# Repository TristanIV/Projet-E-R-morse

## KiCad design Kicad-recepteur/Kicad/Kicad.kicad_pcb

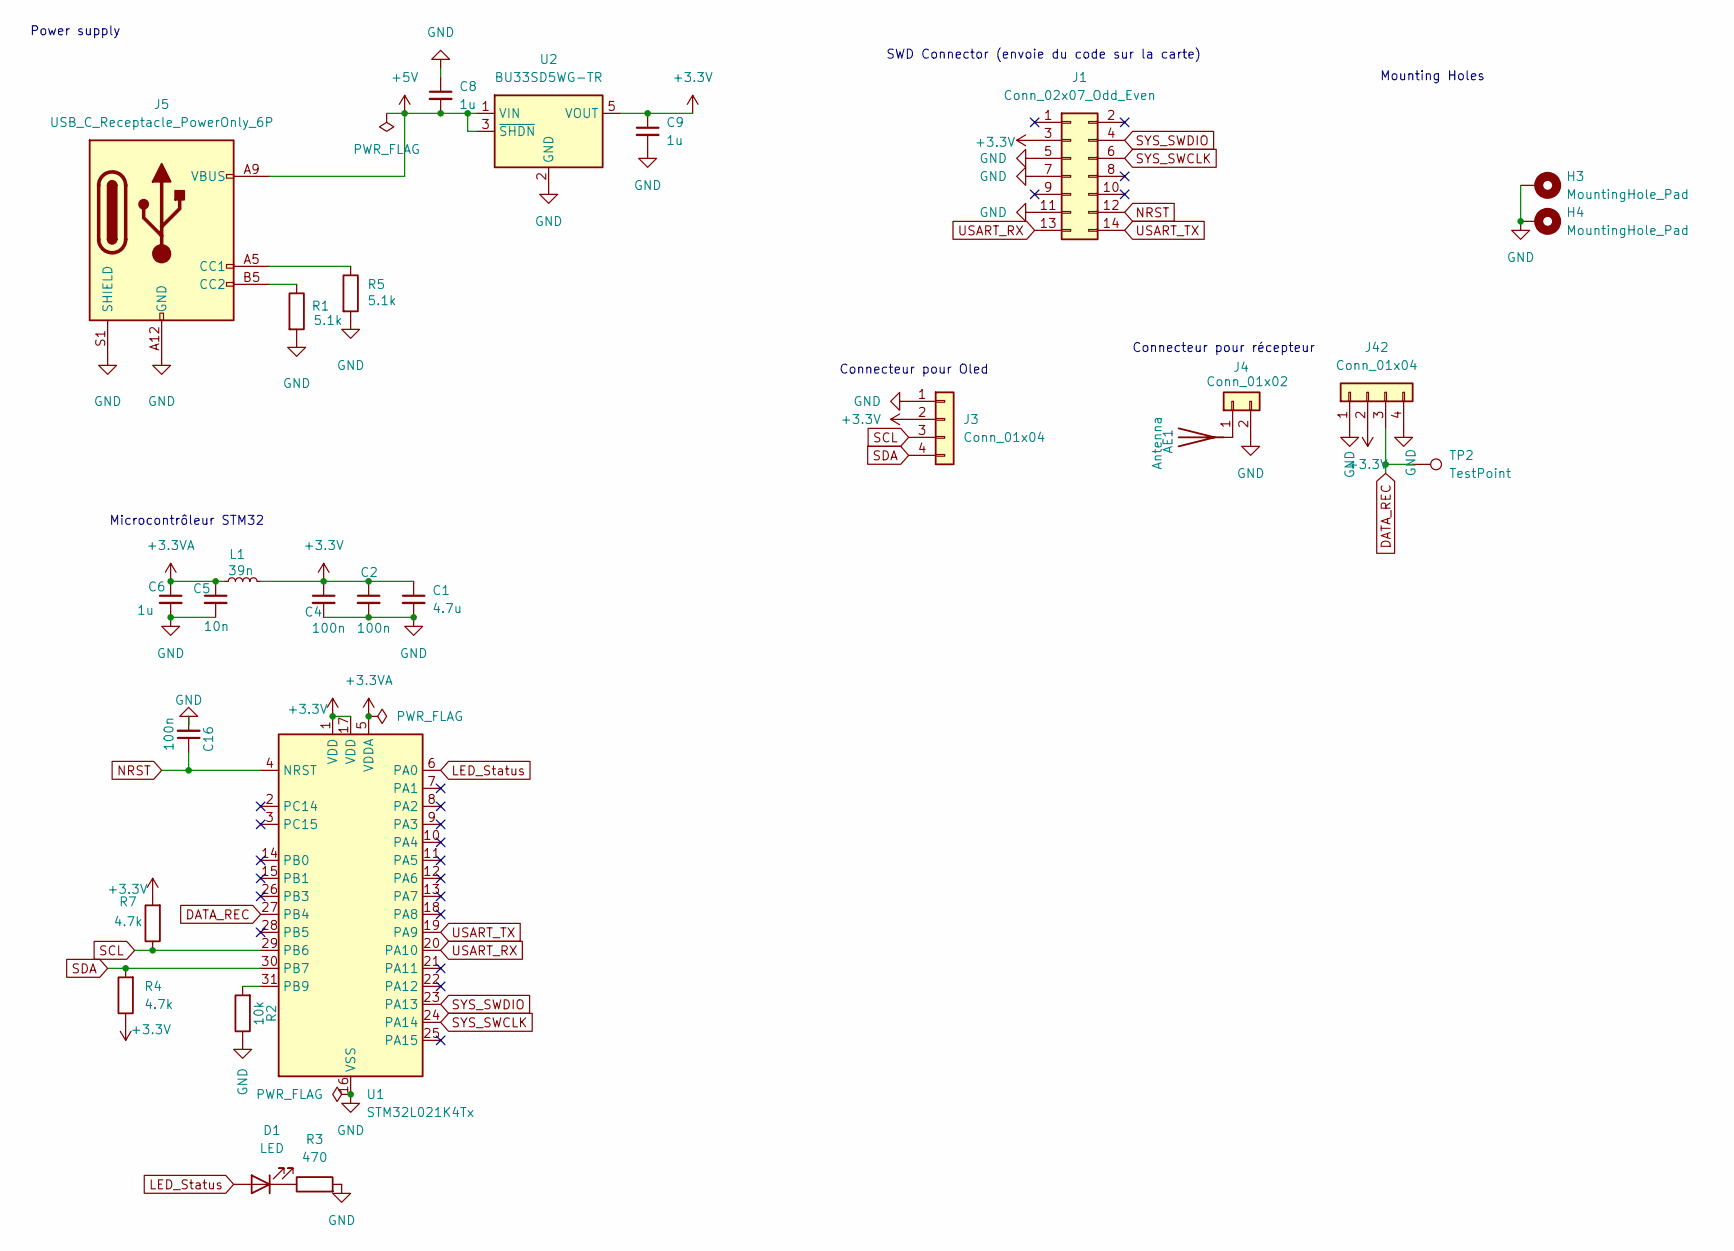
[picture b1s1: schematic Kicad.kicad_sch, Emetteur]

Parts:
AE1: Antenna; SolderWire-0.5sqmm_1x01_D0.9mm_OD2.3mm
C1: 4.7u; C_0603_1608Metric_Pad1.08x0.95mm_HandSolder
C2, C4, C16: 100n; C_0603_1608Metric_Pad1.08x0.95mm_HandSolder
C5: 10n; C_0603_1608Metric_Pad1.08x0.95mm_HandSolder
C6, C8, C9: 1u; C_0603_1608Metric_Pad1.08x0.95mm_HandSolder
D1: LED; LED_0603_1608Metric
H3, H4: MountingHole_Pad; MountingHole_3.2mm_M3_DIN965_Pad
J1: Conn_02x07_Odd_Even; PinHeader_2x07_P1.27mm_Vertical_SMD
J3, J42: Conn_01x04; PinSocket_1x04_P2.54mm_Vertical
J4: Conn_01x02; SolderWire-0.5sqmm_1x02_P4.6mm_D0.9mm_OD2.1mm
J5: USB_C_Receptacle_PowerOnly_6P; USB_C_Receptacle_GCT_USB4125-xx-x-0190_6P_TopMnt_Horizontal
L1: 39n; L_0805_2012Metric_Pad1.05x1.20mm_HandSolder
R1, R5: 5.1k; R_0603_1608Metric_Pad0.98x0.95mm_HandSolder
R2: 10k; R_0603_1608Metric_Pad0.98x0.95mm_HandSolder
R3: 470; R_0603_1608Metric_Pad0.98x0.95mm_HandSolder
R4, R7: 4.7k; R_0603_1608Metric_Pad0.98x0.95mm_HandSolder
TP2: TestPoint; TestPoint_Loop_D2.50mm_Drill1.0mm
U1: STM32L021K4Tx; LQFP-32_7x7mm_P0.8mm
U2: BU33SD5WG-TR; SOT-23-5

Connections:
+3.3V: C1.1, C2.1, C4.1, C9.1, J1.3, J3.2, J42.2, L1.2, R4.1, R7.2, U1.1 (VDD), U1.17 (VDD), U2.5 (VOUT)
+3.3VA: C5.1, C6.1, L1.1, U1.5 (VDDA)
+5V: C8.2, J5.A9 (VBUS), J5.B9 (VBUS), U2.1 (VIN), U2.3 (~SHDN)
DATA_REC: J42.3, TP2.1, U1.27 (PB4)
GND: C1.2, C2.2, C4.2, C5.2, C6.2, C8.1, C9.2, C16.2, H3.1, H4.1, J1.5, J1.7, J1.11, J3.1, J4.2, J5.A12 (GND), J5.B12 (GND), J5.S1 (SHIELD), J42.1, J42.4, R1.2, R2.1, R3.2, R5.2, U1.16 (VSS), U1.32 (VSS), U2.2 (GND)
LED_Status: D1.2 (A), U1.6 (PA0)
NRST: C16.1, J1.12, U1.4 (NRST)
unnamed: AE1.1 (A), J4.1
unnamed: D1.1 (K), R3.1
unnamed: J5.A5 (CC1), R5.1
unnamed: J5.B5 (CC2), R1.1
unnamed: R2.2, U1.31 (PB9)
SCL: J3.3, R7.1, U1.29 (PB6)
SDA: J3.4, R4.2, U1.30 (PB7)
SYS_SWCLK: J1.6, U1.24 (PA14)
SYS_SWDIO: J1.4, U1.23 (PA13)
USART_RX: J1.13, U1.20 (PA10)
USART_TX: J1.14, U1.19 (PA9)

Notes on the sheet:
Connecteur pour Oled
Power supply
SWD Connector (envoie du code sur la carte)
Microcontrôleur STM32
Connecteur pour récepteur
Mounting Holes

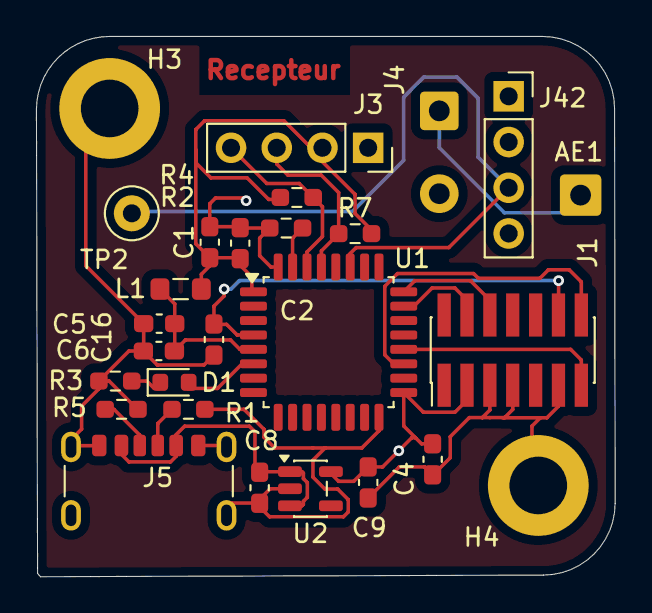
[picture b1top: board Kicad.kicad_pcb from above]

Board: 4 copper layers, 32.2 x 30.0 mm, 27 parts (0 on the bottom side), 18 nets.

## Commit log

2026-02-16 test
2026-02-19 Plus compact pas fini
2026-02-25 feat: Add Kicad project files for the emeteur circuit, including schematic and PCB layout.
2026-03-09 feat: Add initial KiCad project files for the emitter.
2026-03-09 feat: Add initial Kicad PCB design and project files.
2026-03-09 feat: Add Kicad project files for the receiver, including schematic, PCB, and project settings.
2026-03-09 feat: Initial KiCad PCB layout and project files for the receiver module.
2026-03-09 refactor: Reorganize Kicad project files into a `Kicad-recepteur` subfolder, including a new PCB layout, and add a `.gitignore`.
2026-03-09 chore: ignore kicad backups and cache files
2026-03-09 Add Morse_Projet_PCB folder
2026-03-09 Remove an unspecified file.
2026-03-16 feat: Add initial KiCad PCB and schematic files for the receiver project.
2026-03-16 feat: Add initial KiCad project files for emitter and receiver modules.
2026-03-19 feat: Add initial Kicad PCB designs for receiver and emitter, and generate emitter Gerber files.
2026-03-19 feat: Add Kicad project local settings file.
2026-03-19 feat: Add initial KiCad project preference file for the emitter and PCB layout for the receiver.
2026-03-19 feat: Add initial KiCad PCB layout and project files for the receiver.
2026-03-19 feat: Add initial KiCad PCB layout for the receiver module.
